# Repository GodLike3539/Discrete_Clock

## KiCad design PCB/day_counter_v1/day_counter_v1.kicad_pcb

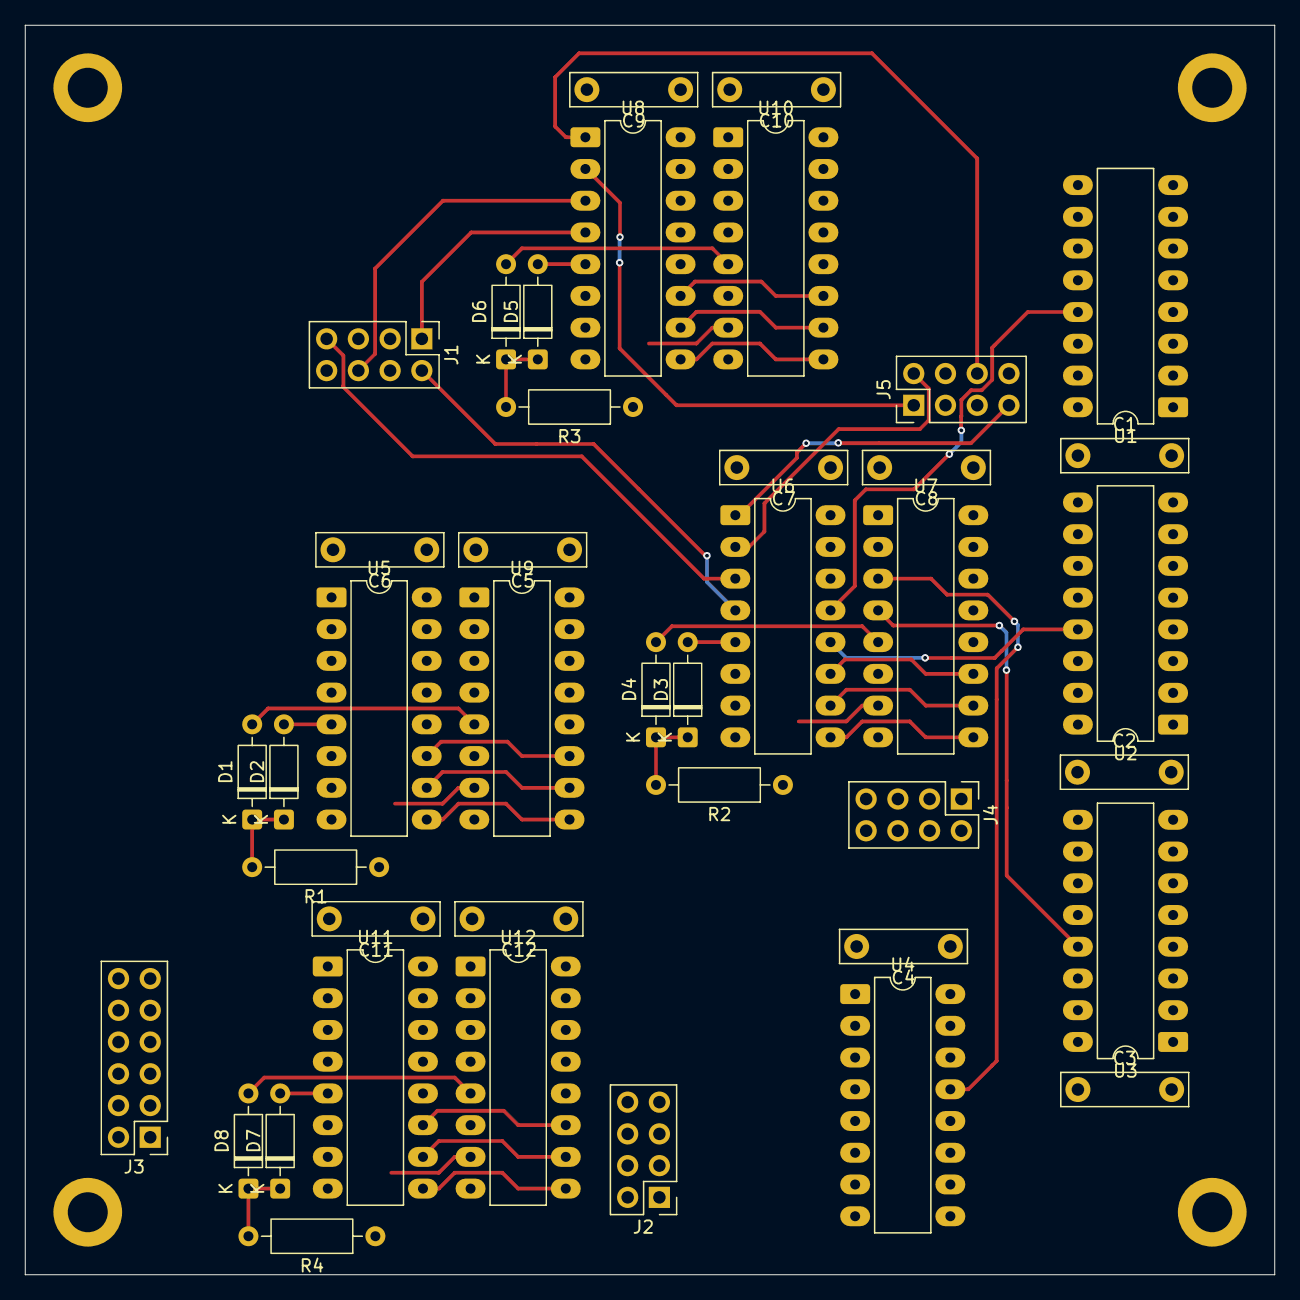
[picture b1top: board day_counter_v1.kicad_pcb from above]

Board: 2 copper layers, 100.0 x 100.0 mm, 45 parts (0 on the bottom side), 61 nets.

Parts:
C1, C2, C3, C4, C5, C6, C7, C8, C9, C10, C11, C12: C; C_Rect_L10.0mm_W2.5mm_P7.50mm_MKS4
D1, D2, D3, D4, D5, D6, D7, D8: 1N4148; D_DO-35_SOD27_P7.62mm_Horizontal
H1, H2, H3, H4: MountingHole_Pad; MountingHole_3.2mm_M3_ISO14580_Pad
J1, J2, J4, J5: Conn_02x04_Odd_Even; PinHeader_2x04_P2.54mm_Vertical
J3: Conn_02x06_Odd_Even; PinHeader_2x06_P2.54mm_Vertical
R1, R2, R3, R4: 1k; R_Axial_DIN0207_L6.3mm_D2.5mm_P10.16mm_Horizontal
U1, U2, U3, U4: 74LS160; DIP-16_W7.62mm_LongPads
U5, U6, U7, U8, U9, U10, U11, U12: 74LS151; DIP-16_W7.62mm_LongPads

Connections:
1PPD: J4.6, U1.7 (CEP)
1dA: U1.14 (Q0), U9.13 (I6)
1dB: U1.13 (Q1), U6.13 (I6)
1dC: U1.12 (Q2), U8.13 (I6)
1dD: U1.11 (Q3), U11.13 (I6)
1hA: J4.4, U9.15 (I4)
1hB: J4.2, U6.15 (I4)
1hC: J4.1, U8.15 (I4)
1hD: J4.3, U11.15 (I4)
1mA: J5.4, U9.2 (I2)
1mB: J5.2, U6.2 (I2)
1mC: J5.1, U8.2 (I2)
1mD: J5.3, U11.2 (I2)
1sA: J1.4, U9.4 (I0)
1sB: J1.2, U6.4 (I0)
1sC: J1.1, U8.4 (I0)
1sD: J1.3, U11.4 (I0)
10dA: U2.14 (Q0), U9.12 (I7)
10dB: U2.13 (Q1), U6.12 (I7)
10dC: U2.12 (Q2), U8.12 (I7)
10dD: U2.11 (Q3), U11.12 (I7)
10hA: J4.5, U9.14 (I5)
10hB: J4.7, U6.14 (I5)
10mA: J5.5, U9.1 (I3)
10mB: J5.7, U6.1 (I3)
10mC: J5.6, U8.1 (I3)
10sA: J1.5, U9.3 (I1)
10sB: J1.7, U6.3 (I1)
10sC: J1.6, U8.3 (I1)
50Hz: U1.2 (CP), U2.2 (CP), U3.2 (CP), U4.2 (CP)
100dA: U3.14 (Q0), U5.4 (I0)
100dB: U3.13 (Q1), U7.4 (I0)
100dC: U3.12 (Q2), U10.4 (I0)
100dD: U3.11 (Q3), U12.4 (I0)
1000dA: U4.14 (Q0), U5.3 (I1)
1000dB: U4.13 (Q1), U7.3 (I1)
1000dC: U4.12 (Q2), U10.3 (I1)
1000dD: U4.11 (Q3), U12.3 (I1)
+5V: C1.1, C2.1, C3.1, C4.1, C5.1, C6.1, C7.1, C8.1, C9.1, C10.1, C11.1, C12.1, J2.7, J2.8, J3.11, U1.1 (~MR), U1.9 (~PE), U1.10 (CET), U1.16 (VCC), U2.1 (~MR), U2.9 (~PE), U2.10 (CET), U2.16 (VCC), U3.1 (~MR), U3.9 (~PE), U3.10 (CET), U3.16 (VCC), U4.1 (~MR), U4.9 (~PE), U4.10 (CET), U4.16 (VCC), U5.16 (VCC), U6.16 (VCC), U7.16 (VCC), U8.16 (VCC), U9.16 (VCC), U10.16 (VCC), U11.16 (VCC), U12.16 (VCC)
A: D1.1 (K), D2.1 (K), J3.1, R1.2
B: D3.1 (K), D4.1 (K), J3.2, R2.2
C: D5.1 (K), D6.1 (K), J3.3, R3.2
CLK50: J2.5, J3.10
D: D7.1 (K), D8.1 (K), J3.4, R4.2
GND: C1.2, C2.2, C3.2, C4.2, C5.2, C6.2, C7.2, C8.2, C9.2, C10.2, C11.2, C12.2, J1.8, J2.1, J2.2, J3.12, J4.8, J5.8, R1.1, R2.1, R3.1, R4.1, U1.3 (D0), U1.4 (D1), U1.5 (D2), U1.6 (D3), U1.8 (GND), U2.3 (D0), U2.4 (D1), U2.5 (D2), U2.6 (D3), U2.8 (GND), U3.3 (D0), U3.4 (D1), U3.5 (D2), U3.6 (D3), U3.8 (GND), U4.3 (D0), U4.4 (D1), U4.5 (D2), U4.6 (D3), U4.8 (GND), U5.8 (GND), U6.8 (GND), U7.8 (GND), U8.8 (GND), U9.8 (GND), U10.8 (GND), U11.8 (GND), U12.8 (GND)
unnamed: D1.2 (A), U9.5 (Z)
unnamed: D2.2 (A), U5.5 (Z)
unnamed: D3.2 (A), U6.5 (Z)
unnamed: D4.2 (A), U7.5 (Z)
unnamed: D5.2 (A), U8.5 (Z)
unnamed: D6.2 (A), U10.5 (Z)
unnamed: D7.2 (A), U11.5 (Z)
unnamed: D8.2 (A), U12.5 (Z)
unnamed: U1.15 (TC), U2.7 (CEP)
unnamed: U2.15 (TC), U3.7 (CEP)
unnamed: U3.15 (TC), U4.7 (CEP)
Sel_A: J3.5, U5.11 (S0), U6.11 (S0), U7.11 (S0), U8.11 (S0), U9.11 (S0), U10.11 (S0), U11.11 (S0), U12.11 (S0)
Sel_B: J3.6, U5.10 (S1), U6.10 (S1), U7.10 (S1), U8.10 (S1), U9.10 (S1), U10.10 (S1), U11.10 (S1), U12.10 (S1)
Sel_C: J3.7, U5.9 (S2), U6.9 (S2), U7.9 (S2), U8.9 (S2), U9.9 (S2), U10.9 (S2), U11.9 (S2), U12.9 (S2)
Sel_D: J3.8, U6.7 (~E), U8.7 (~E), U9.7 (~E), U11.7 (~E)
~Sel_D: J3.9, U5.7 (~E), U7.7 (~E), U10.7 (~E), U12.7 (~E)

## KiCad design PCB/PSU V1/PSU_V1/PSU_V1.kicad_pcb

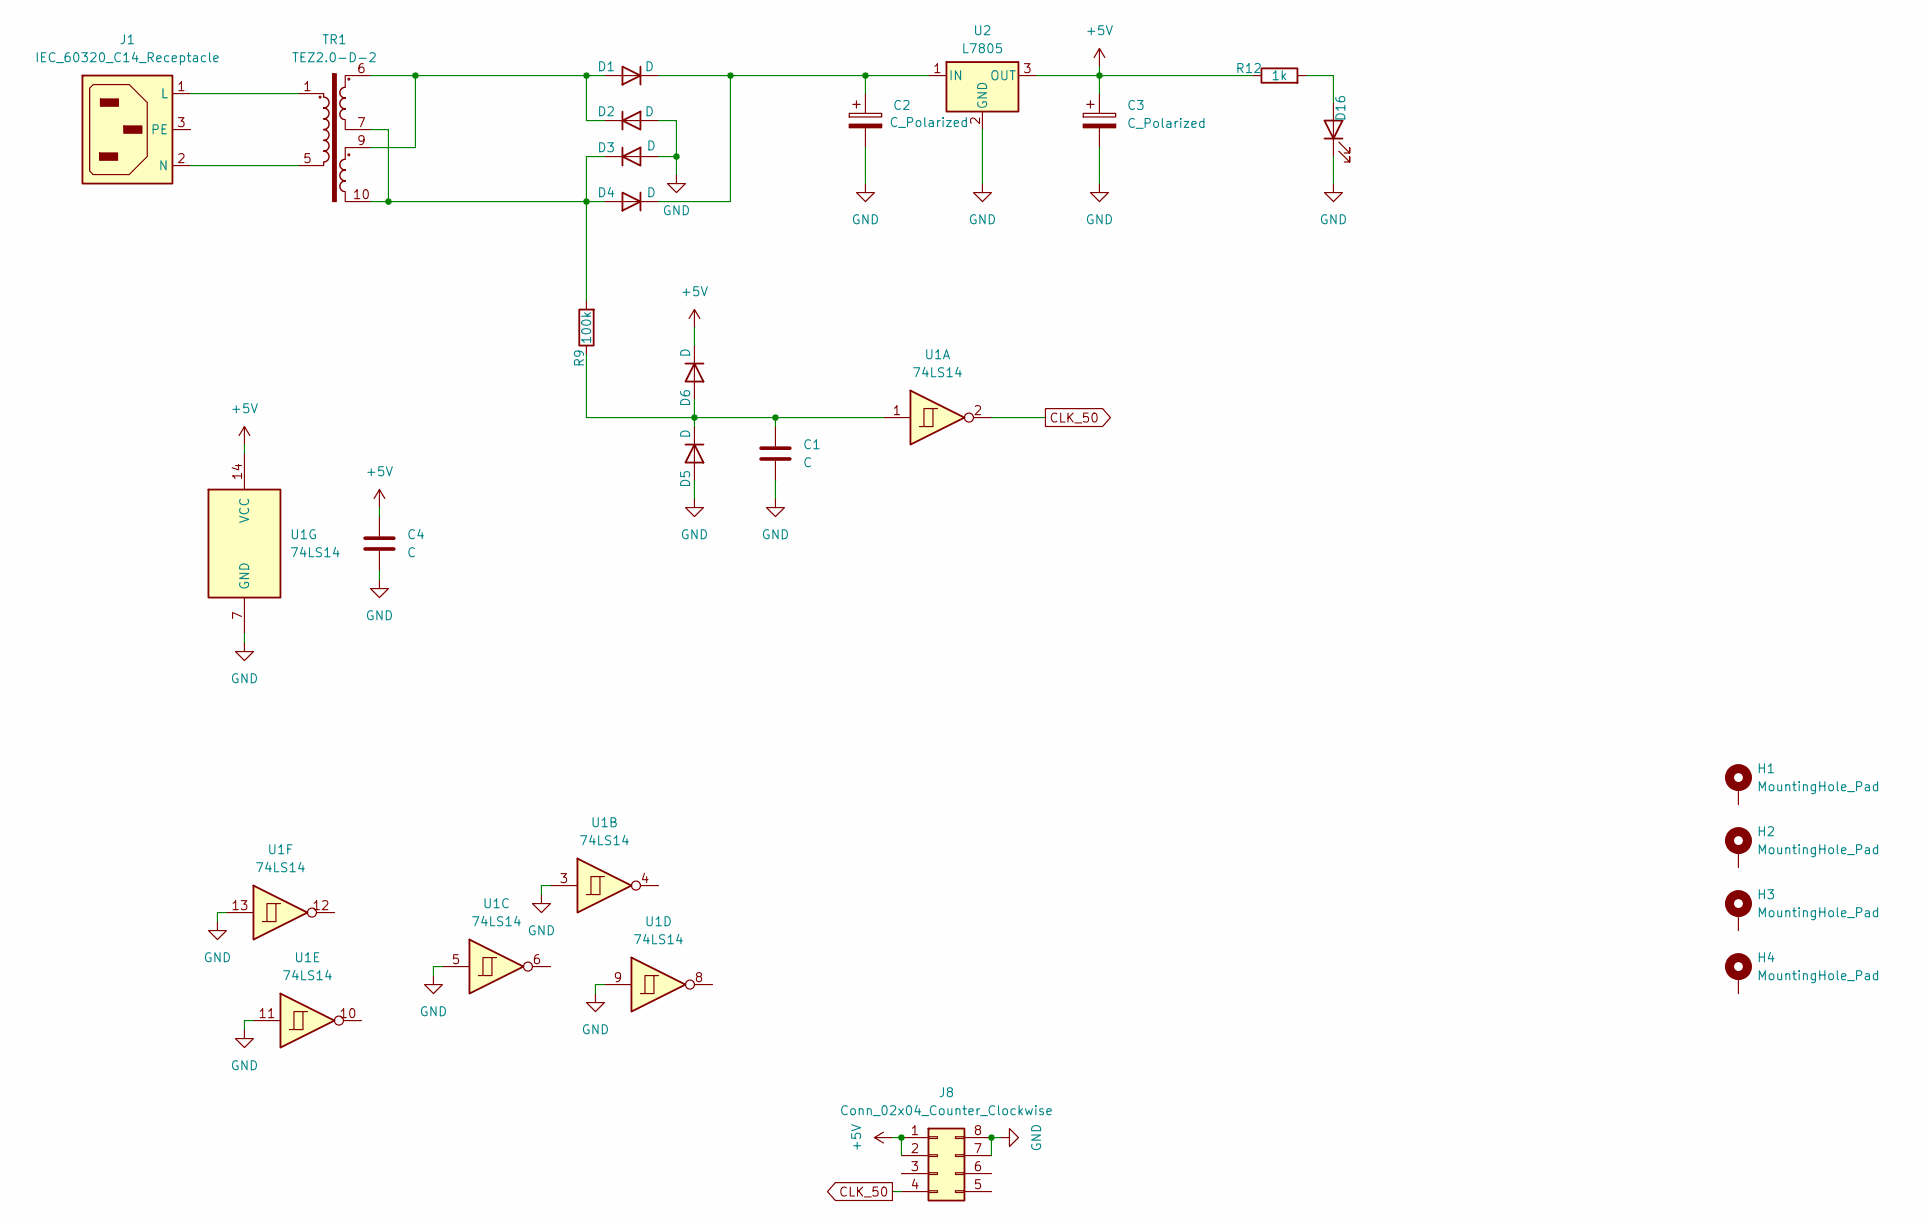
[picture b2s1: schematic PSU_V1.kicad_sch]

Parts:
C1, C4: C; C_Rect_L10.0mm_W2.5mm_P7.50mm_MKS4
C2, C3: C_Polarized; CP_Radial_D12.5mm_P7.50mm
D1, D2, D3, D4, D5, D6: D; D_DO-35_SOD27_P10.16mm_Horizontal
D16: LED; LED_D3.0mm
H1, H2, H3, H4: MountingHole_Pad; MountingHole_3.2mm_M3_DIN965_Pad
J1: IEC_60320_C14_Receptacle; GSF1220161
J8: Conn_02x04_Counter_Clockwise; IDC-Header_2x04_P2.54mm_Vertical
R9: 100k; R_Axial_DIN0207_L6.3mm_D2.5mm_P10.16mm_Horizontal
R12: 1k; R_Axial_DIN0207_L6.3mm_D2.5mm_P10.16mm_Horizontal
TR1: TEZ2.0-D-2; Transformer_CHK_EI42-5VA_2xSec
U1: 74LS14; DIP-14_W7.62mm_LongPads
U2: L7805; TO-220-3_Horizontal_TabDown

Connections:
+5V: C3.1, C4.1, D6.1 (K), J8.1, J8.2, R12.1, U1.14 (VCC), U2.3 (OUT)
CLK_50: J8.4, U1.2
GND: C1.2, C2.2, C3.2, C4.2, D2.2 (A), D3.2 (A), D5.2 (A), D16.1 (K), J8.7, J8.8, U1.3, U1.5, U1.7 (GND), U1.9, U1.11, U1.13, U2.2 (GND)
unnamed: D1.2 (A), D2.1 (K), TR1.6, TR1.9
unnamed: C2.1, D1.1 (K), D4.1 (K), U2.1 (IN)
unnamed: D3.1 (K), D4.2 (A), R9.2, TR1.7, TR1.10
unnamed: C1.1, D5.1 (K), D6.2 (A), R9.1, U1.1
unnamed: D16.2 (A), R12.2
unnamed: J1.1 (L), TR1.1
unnamed: J1.2 (N), TR1.5

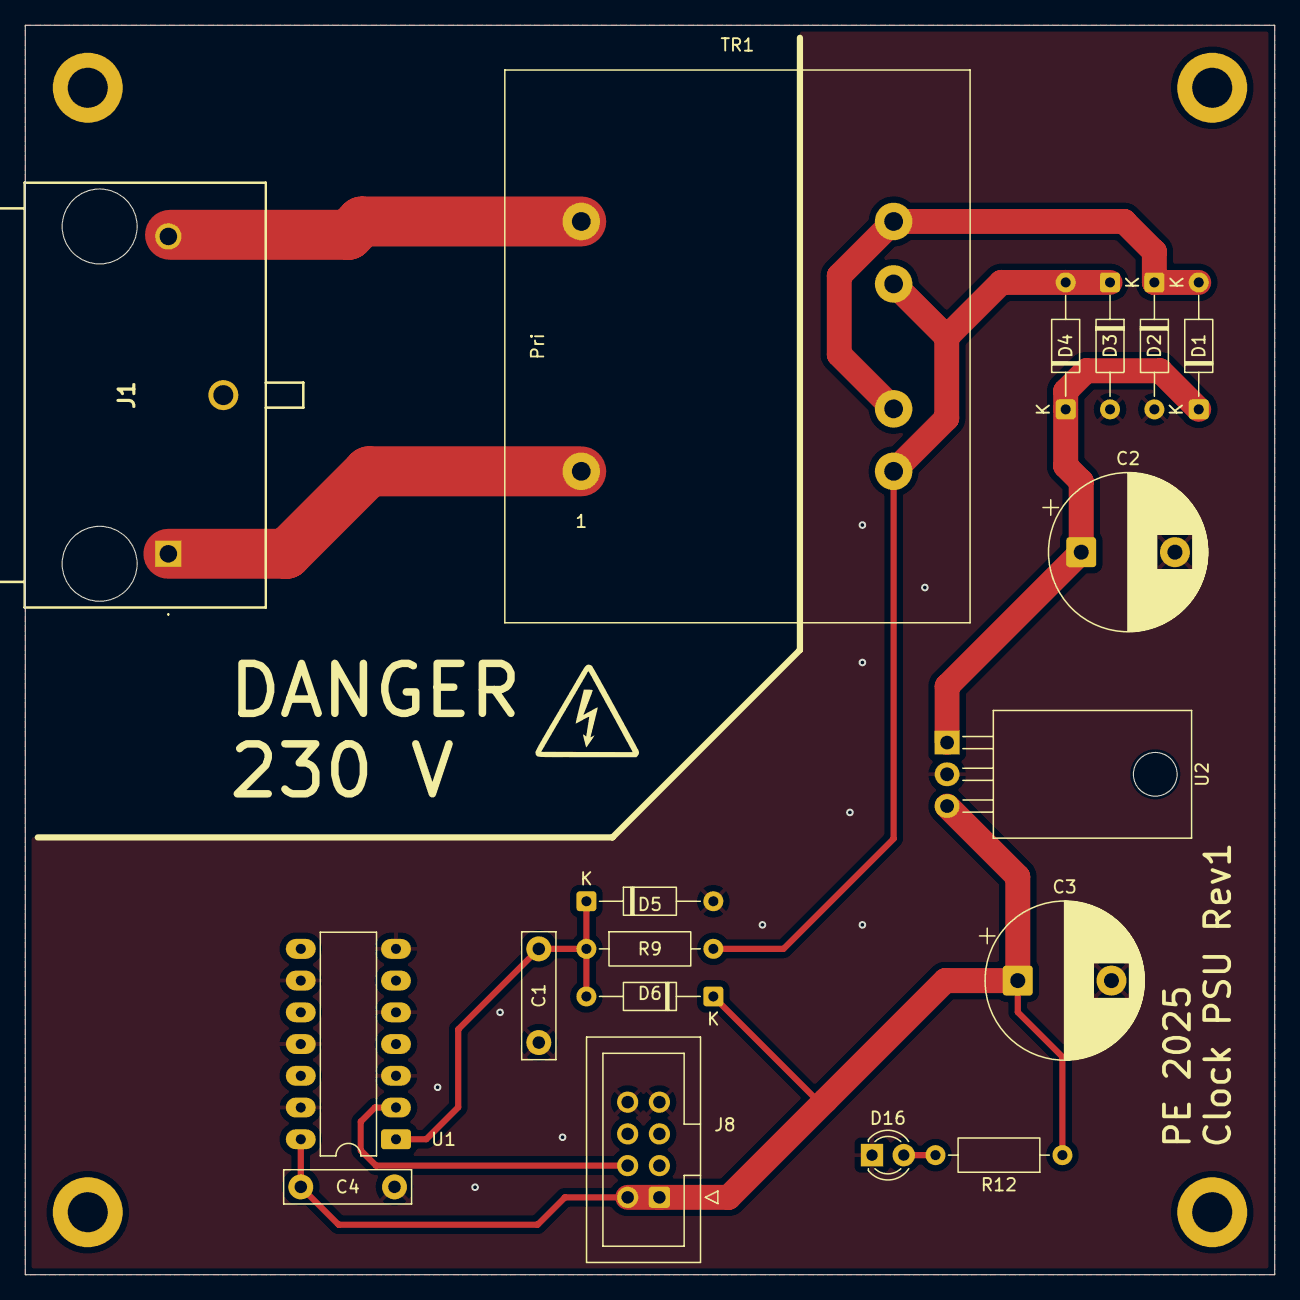
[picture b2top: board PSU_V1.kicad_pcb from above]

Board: 2 copper layers, 100.0 x 100.0 mm, 22 parts (0 on the bottom side), 10 nets.

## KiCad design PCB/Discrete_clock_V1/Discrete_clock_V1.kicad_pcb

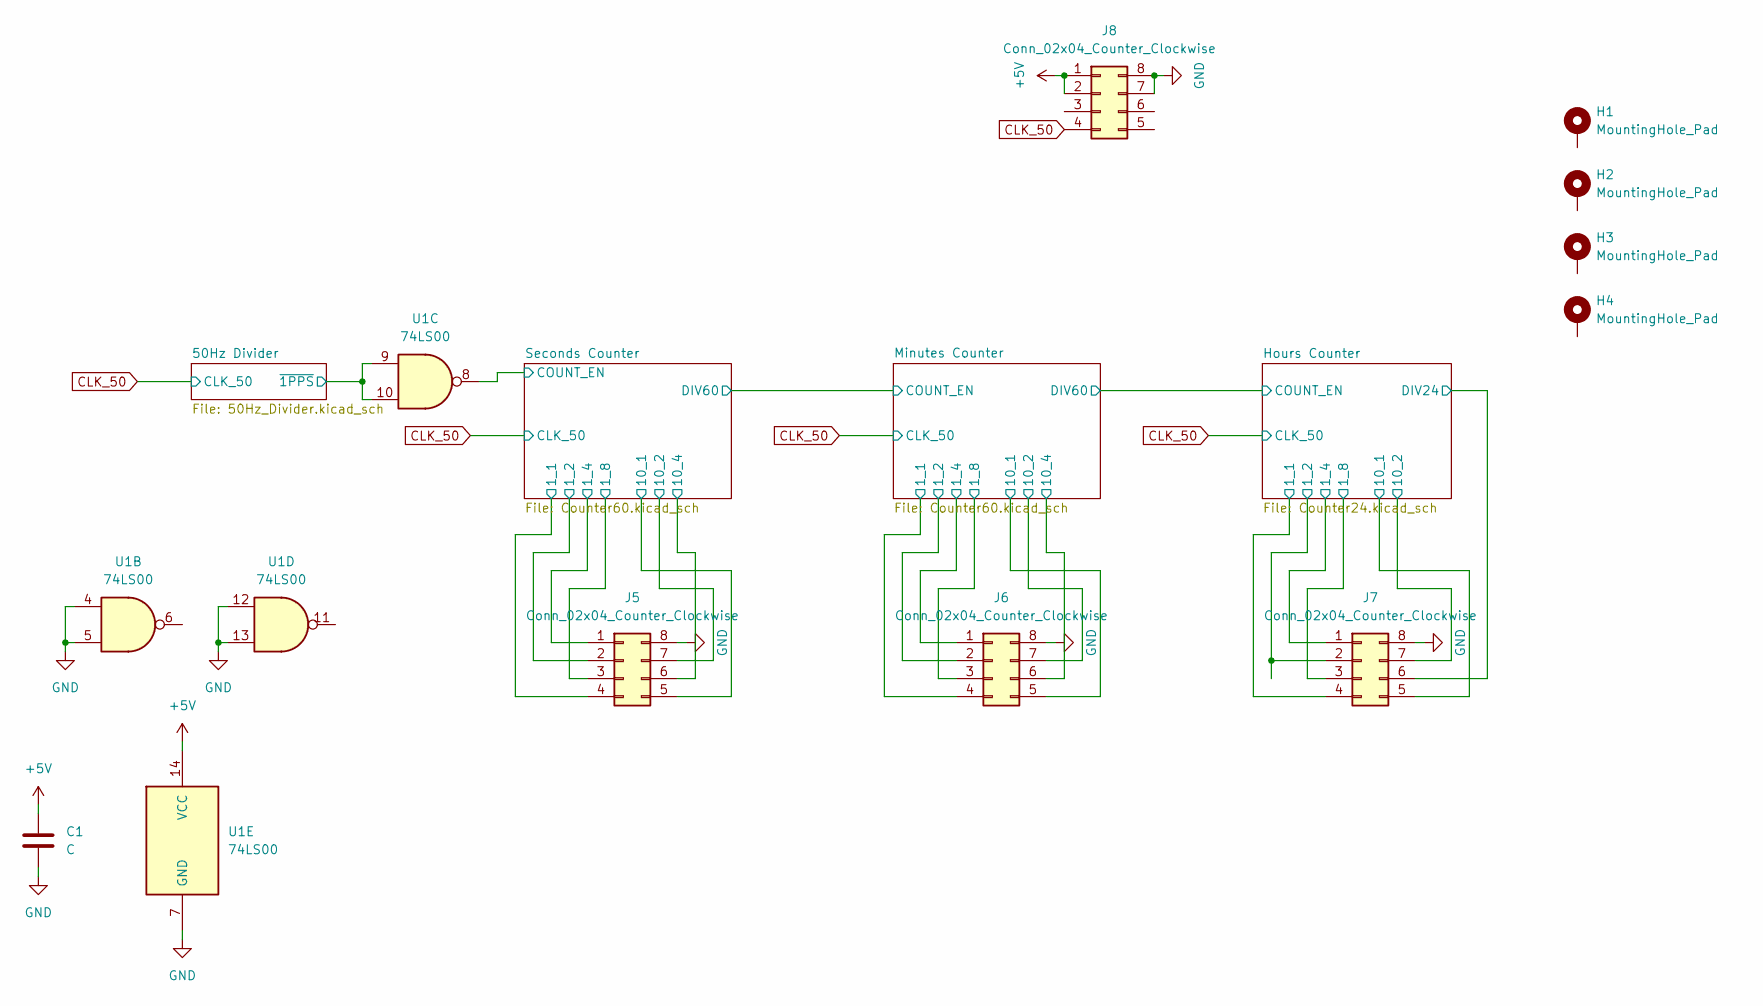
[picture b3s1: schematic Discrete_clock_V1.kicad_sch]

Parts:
C1: C; C_Rect_L10.0mm_W2.5mm_P7.50mm_MKS4
H1, H2, H3, H4: MountingHole_Pad; MountingHole_3.2mm_M3_DIN965_Pad
J5, J6, J7, J8: Conn_02x04_Counter_Clockwise; IDC-Header_2x04_P2.54mm_Vertical
U1: 74LS00; DIP-14_W7.62mm_LongPads

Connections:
+5V: C1.1, J8.1, J8.2, U1.14 (VCC); also elsewhere on the board
/50Hz Divider/~1PPS: U1.9, U1.10; also elsewhere on the board
/Hours Counter/1_1: J7.4; also elsewhere on the board
/Hours Counter/1_2: J7.2; also elsewhere on the board
/Hours Counter/1_4: J7.1; also elsewhere on the board
/Hours Counter/1_8: J7.3; also elsewhere on the board
/Hours Counter/10_1: J7.5; also elsewhere on the board
/Hours Counter/10_2: J7.7; also elsewhere on the board
/Hours Counter/DIV24: J7.6; also elsewhere on the board
/Minutes Counter/1_1: J6.4; also elsewhere on the board
/Minutes Counter/1_2: J6.2; also elsewhere on the board
/Minutes Counter/1_4: J6.1; also elsewhere on the board
/Minutes Counter/1_8: J6.3; also elsewhere on the board
/Minutes Counter/10_1: J6.5; also elsewhere on the board
/Minutes Counter/10_2: J6.7; also elsewhere on the board
/Minutes Counter/10_4: J6.6; also elsewhere on the board
/Seconds Counter/1_1: J5.4; also elsewhere on the board
/Seconds Counter/1_2: J5.2; also elsewhere on the board
/Seconds Counter/1_4: J5.1; also elsewhere on the board
/Seconds Counter/1_8: J5.3; also elsewhere on the board
/Seconds Counter/10_1: J5.5; also elsewhere on the board
/Seconds Counter/10_2: J5.7; also elsewhere on the board
/Seconds Counter/10_4: J5.6; also elsewhere on the board
/Seconds Counter/COUNT_EN: U1.8; also elsewhere on the board
CLK_50: J8.4; also elsewhere on the board
GND: C1.2, J5.8, J6.8, J7.8, J8.7, J8.8, U1.4, U1.5, U1.7 (GND), U1.12, U1.13; also elsewhere on the board

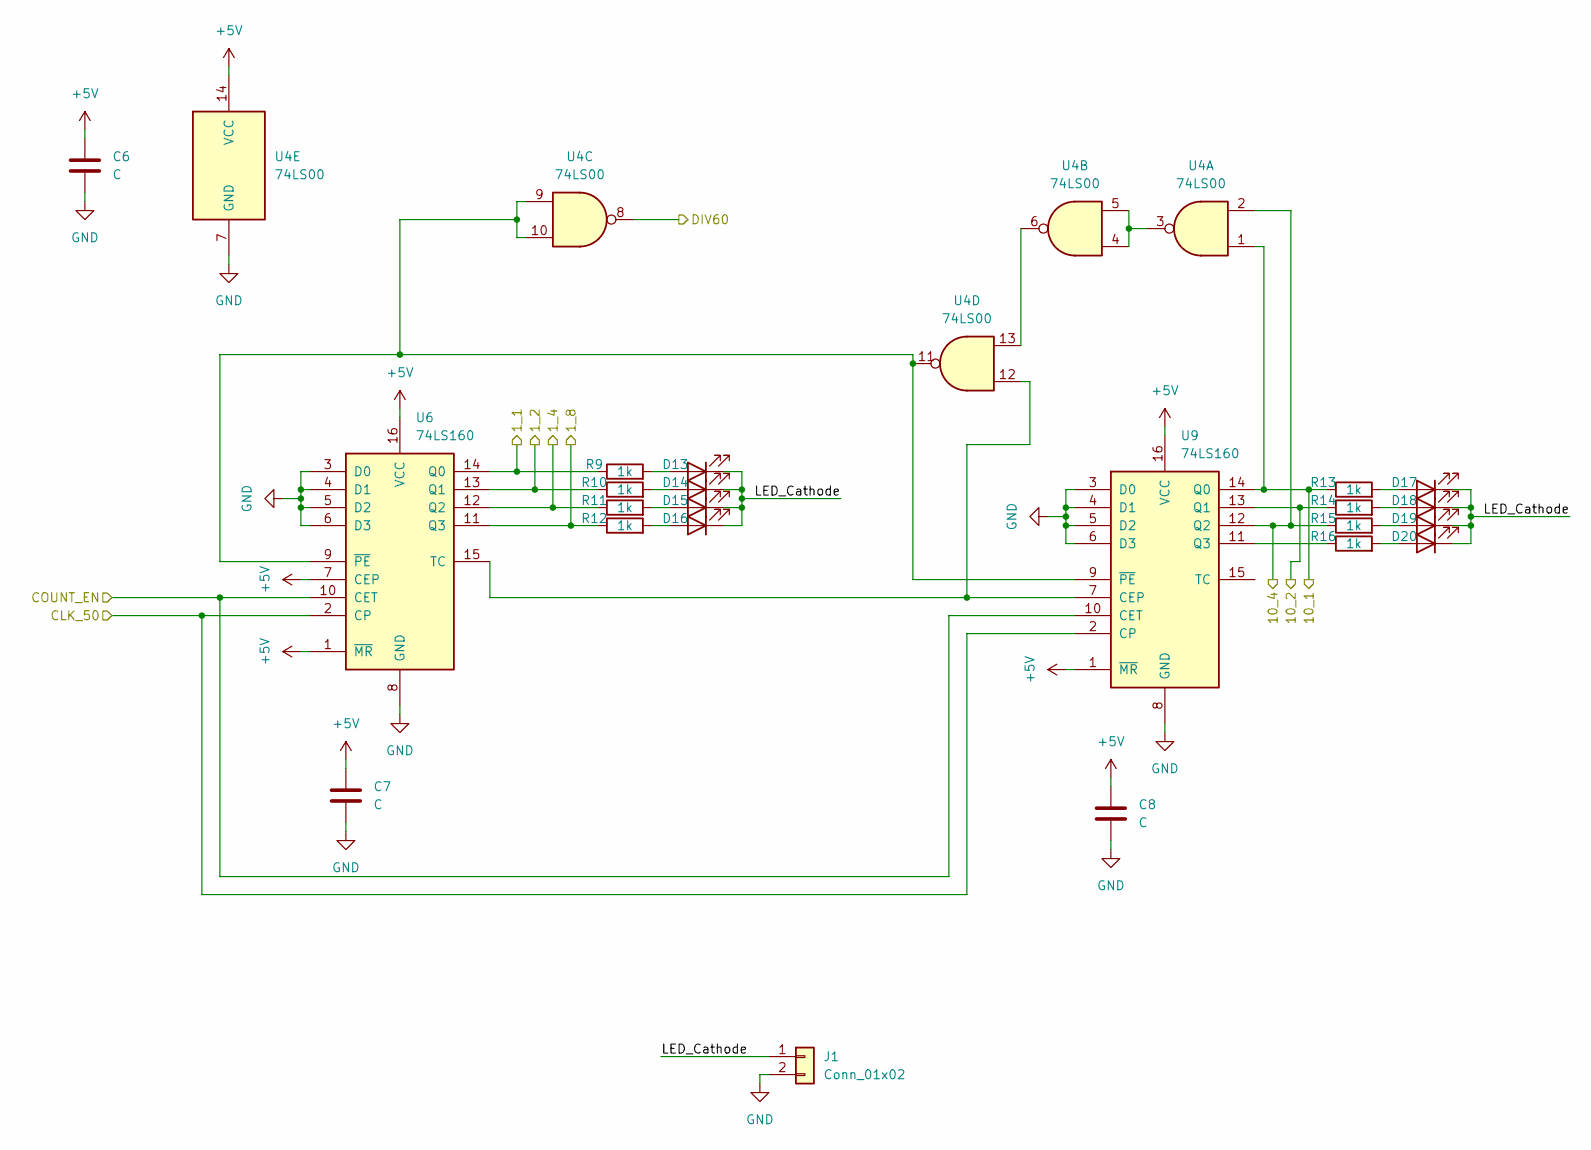
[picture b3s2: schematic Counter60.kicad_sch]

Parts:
C6, C7, C8: C; C_Rect_L10.0mm_W2.5mm_P7.50mm_MKS4
D13, D14, D15, D16, D17, D18, D19, D20: LED; LED_D3.0mm
J1: Conn_01x02; PinHeader_1x02_P2.54mm_Vertical
R9, R10, R11, R12, R13, R14, R15, R16: 1k; R_Axial_DIN0207_L6.3mm_D2.5mm_P10.16mm_Horizontal
U4: 74LS00; DIP-14_W7.62mm_LongPads
U6, U9: 74LS160; DIP-16_W7.62mm_LongPads

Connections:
+5V: C6.1, C7.1, C8.1, U4.14 (VCC), U6.1 (~MR), U6.7 (CEP), U6.16 (VCC), U9.1 (~MR), U9.16 (VCC); also elsewhere on the board
/Minutes Counter/COUNT_EN: U4.8; also elsewhere on the board
/Seconds Counter/1_1: R9.1, U6.14 (Q0); also elsewhere on the board
/Seconds Counter/1_2: R10.1, U6.13 (Q1); also elsewhere on the board
/Seconds Counter/1_4: R11.1, U6.12 (Q2); also elsewhere on the board
/Seconds Counter/1_8: R12.1, U6.11 (Q3); also elsewhere on the board
/Seconds Counter/10_1: R13.1, U4.1, U9.14 (Q0); also elsewhere on the board
/Seconds Counter/10_2: R14.1, U9.13 (Q1); also elsewhere on the board
/Seconds Counter/10_4: R15.1, U4.2, U9.12 (Q2); also elsewhere on the board
/Seconds Counter/COUNT_EN: U6.10 (CET), U9.10 (CET); also elsewhere on the board
/Seconds Counter/LED_Cathode: D13.1 (K), D14.1 (K), D15.1 (K), D16.1 (K), D17.1 (K), D18.1 (K), D19.1 (K), D20.1 (K), J1.1
CLK_50: U6.2 (CP), U9.2 (CP); also elsewhere on the board
GND: C6.2, C7.2, C8.2, J1.2, U4.7 (GND), U6.3 (D0), U6.4 (D1), U6.5 (D2), U6.6 (D3), U6.8 (GND), U9.3 (D0), U9.4 (D1), U9.5 (D2), U9.6 (D3), U9.8 (GND); also elsewhere on the board
unnamed: D13.2 (A), R9.2
unnamed: D14.2 (A), R10.2
unnamed: D15.2 (A), R11.2
unnamed: D16.2 (A), R12.2
unnamed: D17.2 (A), R13.2
unnamed: D18.2 (A), R14.2
unnamed: D19.2 (A), R15.2
unnamed: D20.2 (A), R16.2
unnamed: U4.3, U4.4, U4.5
unnamed: U4.6, U4.13
unnamed: U4.12, U6.15 (TC), U9.7 (CEP)
unnamed: U4.9, U4.10, U4.11, U6.9 (~PE), U9.9 (~PE)
unnamed: R16.1, U9.11 (Q3)

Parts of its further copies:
C9, C10, C11: C; C_Rect_L10.0mm_W2.5mm_P7.50mm_MKS4
D21, D22, D23, D24, D25, D26, D27, D28: LED; LED_D3.0mm
J2: Conn_01x02; PinHeader_1x02_P2.54mm_Vertical
R17, R18, R19, R20, R21, R22, R23, R24: 1k; R_Axial_DIN0207_L6.3mm_D2.5mm_P10.16mm_Horizontal
U7: 74LS00; DIP-14_W7.62mm_LongPads
U10, U12: 74LS160; DIP-16_W7.62mm_LongPads

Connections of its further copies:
+5V: C9.1, C10.1, C11.1, U7.14 (VCC), U10.1 (~MR), U10.7 (CEP), U10.16 (VCC), U12.1 (~MR), U12.16 (VCC); also elsewhere on the board
/Hours Counter/COUNT_EN: U7.11; also elsewhere on the board
/Minutes Counter/1_1: R17.1, U10.14 (Q0); also elsewhere on the board
/Minutes Counter/1_2: R18.1, U10.13 (Q1); also elsewhere on the board
/Minutes Counter/1_4: R19.1, U10.12 (Q2); also elsewhere on the board
/Minutes Counter/1_8: R20.1, U10.11 (Q3); also elsewhere on the board
/Minutes Counter/10_1: R21.1, U7.1, U12.14 (Q0); also elsewhere on the board
/Minutes Counter/10_2: R22.1, U12.13 (Q1); also elsewhere on the board
/Minutes Counter/10_4: R23.1, U7.2, U12.12 (Q2); also elsewhere on the board
/Minutes Counter/COUNT_EN: U10.10 (CET), U12.10 (CET); also elsewhere on the board
/Minutes Counter/LED_Cathode: D21.1 (K), D22.1 (K), D23.1 (K), D24.1 (K), D25.1 (K), D26.1 (K), D27.1 (K), D28.1 (K), J2.1
CLK_50: U10.2 (CP), U12.2 (CP); also elsewhere on the board
GND: C9.2, C10.2, C11.2, J2.2, U7.7 (GND), U10.3 (D0), U10.4 (D1), U10.5 (D2), U10.6 (D3), U10.8 (GND), U12.3 (D0), U12.4 (D1), U12.5 (D2), U12.6 (D3), U12.8 (GND); also elsewhere on the board
unnamed: D21.2 (A), R17.2
unnamed: D22.2 (A), R18.2
unnamed: D23.2 (A), R19.2
unnamed: D24.2 (A), R20.2
unnamed: D25.2 (A), R21.2
unnamed: D26.2 (A), R22.2
unnamed: D27.2 (A), R23.2
unnamed: D28.2 (A), R24.2
unnamed: U7.3, U7.4, U7.5
unnamed: U7.6, U7.10
unnamed: U7.9, U10.15 (TC), U12.7 (CEP)
unnamed: U7.8, U7.12, U7.13, U10.9 (~PE), U12.9 (~PE)
unnamed: R24.1, U12.11 (Q3)

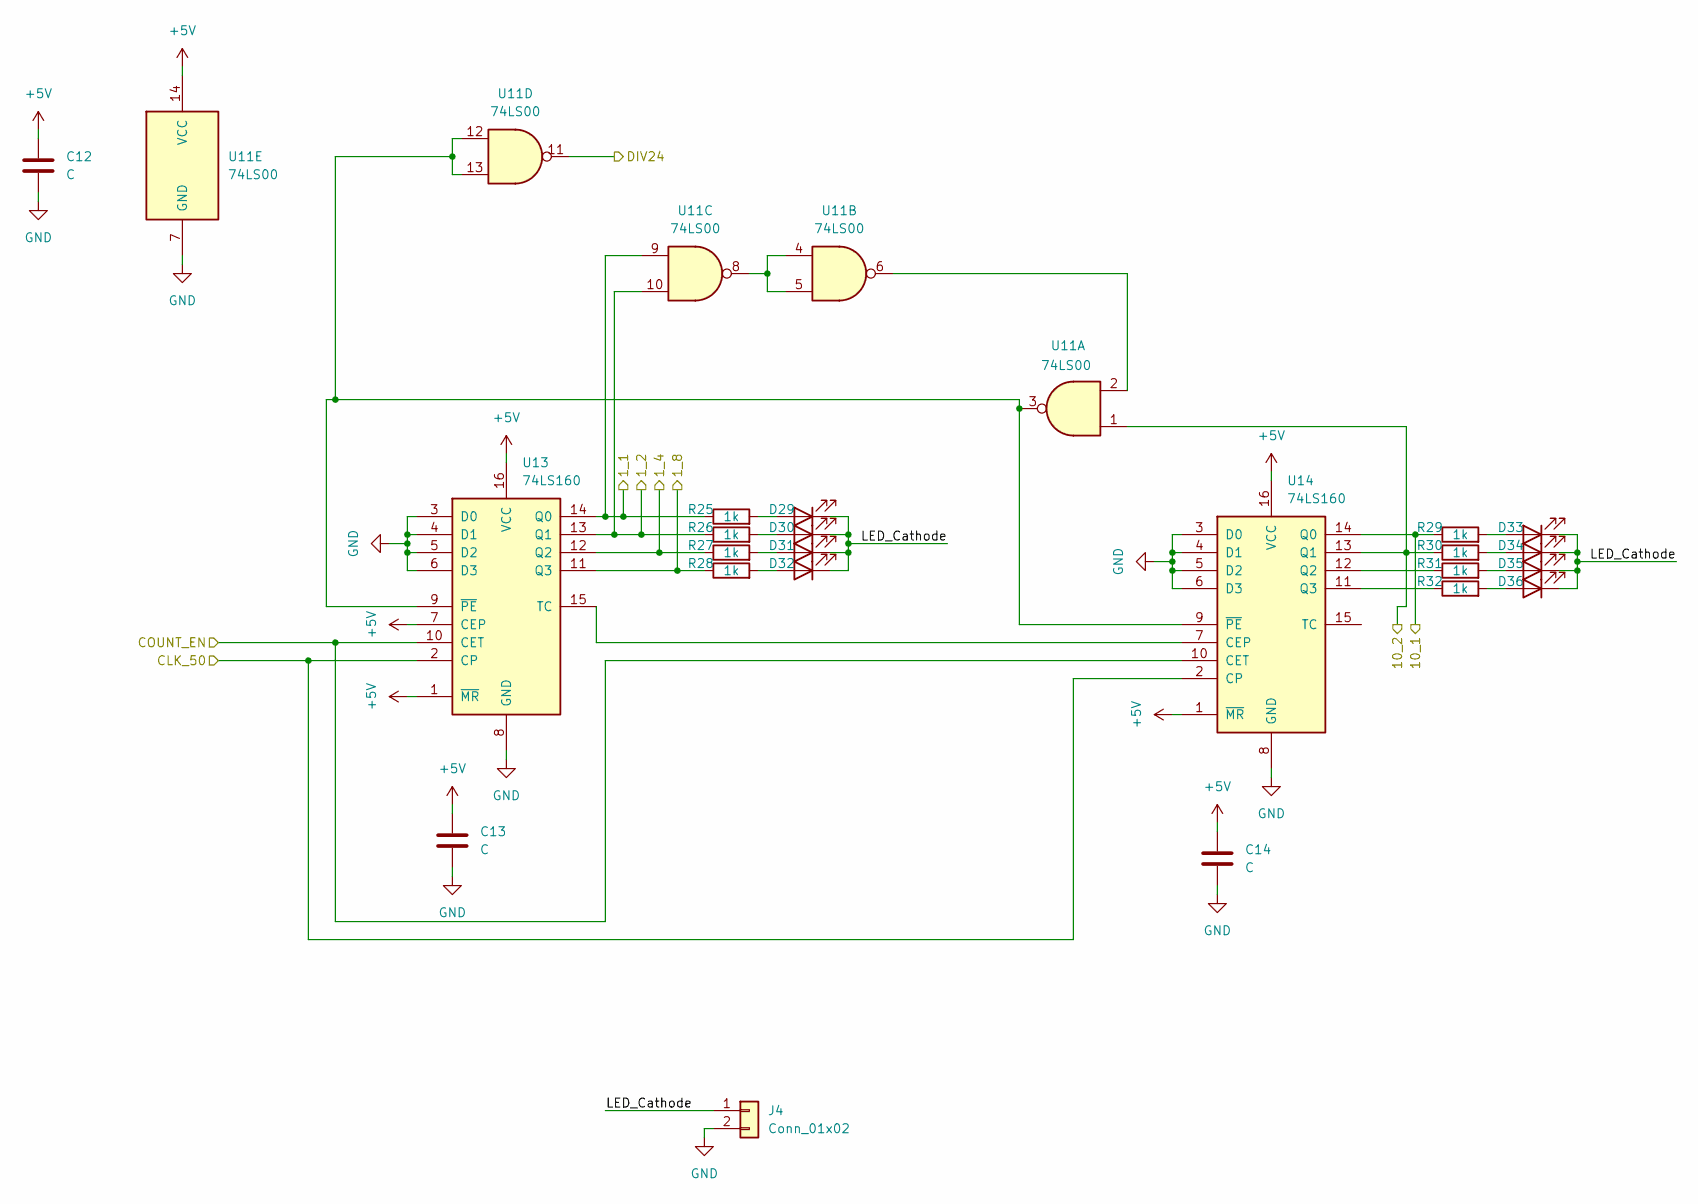
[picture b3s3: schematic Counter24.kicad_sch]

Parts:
C12, C13, C14: C; C_Rect_L10.0mm_W2.5mm_P7.50mm_MKS4
D29, D30, D31, D32, D33, D34, D35, D36: LED; LED_D3.0mm
J4: Conn_01x02; PinHeader_1x02_P2.54mm_Vertical
R25, R26, R27, R28, R29, R30, R31, R32: 1k; R_Axial_DIN0207_L6.3mm_D2.5mm_P10.16mm_Horizontal
U11: 74LS00; DIP-14_W7.62mm_LongPads
U13, U14: 74LS160; DIP-16_W7.62mm_LongPads

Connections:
+5V: C12.1, C13.1, C14.1, U11.14 (VCC), U13.1 (~MR), U13.7 (CEP), U13.16 (VCC), U14.1 (~MR), U14.16 (VCC); also elsewhere on the board
/Hours Counter/1_1: R25.1, U11.9, U13.14 (Q0); also elsewhere on the board
/Hours Counter/1_2: R26.1, U11.10, U13.13 (Q1); also elsewhere on the board
/Hours Counter/1_4: R27.1, U13.12 (Q2); also elsewhere on the board
/Hours Counter/1_8: R28.1, U13.11 (Q3); also elsewhere on the board
/Hours Counter/10_1: R29.1, U14.14 (Q0); also elsewhere on the board
/Hours Counter/10_2: R30.1, U11.1, U14.13 (Q1); also elsewhere on the board
/Hours Counter/COUNT_EN: U13.10 (CET), U14.10 (CET); also elsewhere on the board
/Hours Counter/DIV24: U11.11; also elsewhere on the board
/Hours Counter/LED_Cathode: D29.1 (K), D30.1 (K), D31.1 (K), D32.1 (K), D33.1 (K), D34.1 (K), D35.1 (K), D36.1 (K), J4.1
CLK_50: U13.2 (CP), U14.2 (CP); also elsewhere on the board
GND: C12.2, C13.2, C14.2, J4.2, U11.7 (GND), U13.3 (D0), U13.4 (D1), U13.5 (D2), U13.6 (D3), U13.8 (GND), U14.3 (D0), U14.4 (D1), U14.5 (D2), U14.6 (D3), U14.8 (GND); also elsewhere on the board
unnamed: D29.2 (A), R25.2
unnamed: D30.2 (A), R26.2
unnamed: D31.2 (A), R27.2
unnamed: D32.2 (A), R28.2
unnamed: D33.2 (A), R29.2
unnamed: D34.2 (A), R30.2
unnamed: D35.2 (A), R31.2
unnamed: D36.2 (A), R32.2
unnamed: U11.2, U11.6
unnamed: U11.4, U11.5, U11.8
unnamed: U13.15 (TC), U14.7 (CEP)
unnamed: U11.3, U11.12, U11.13, U13.9 (~PE), U14.9 (~PE)
unnamed: R31.1, U14.12 (Q2)
unnamed: R32.1, U14.11 (Q3)

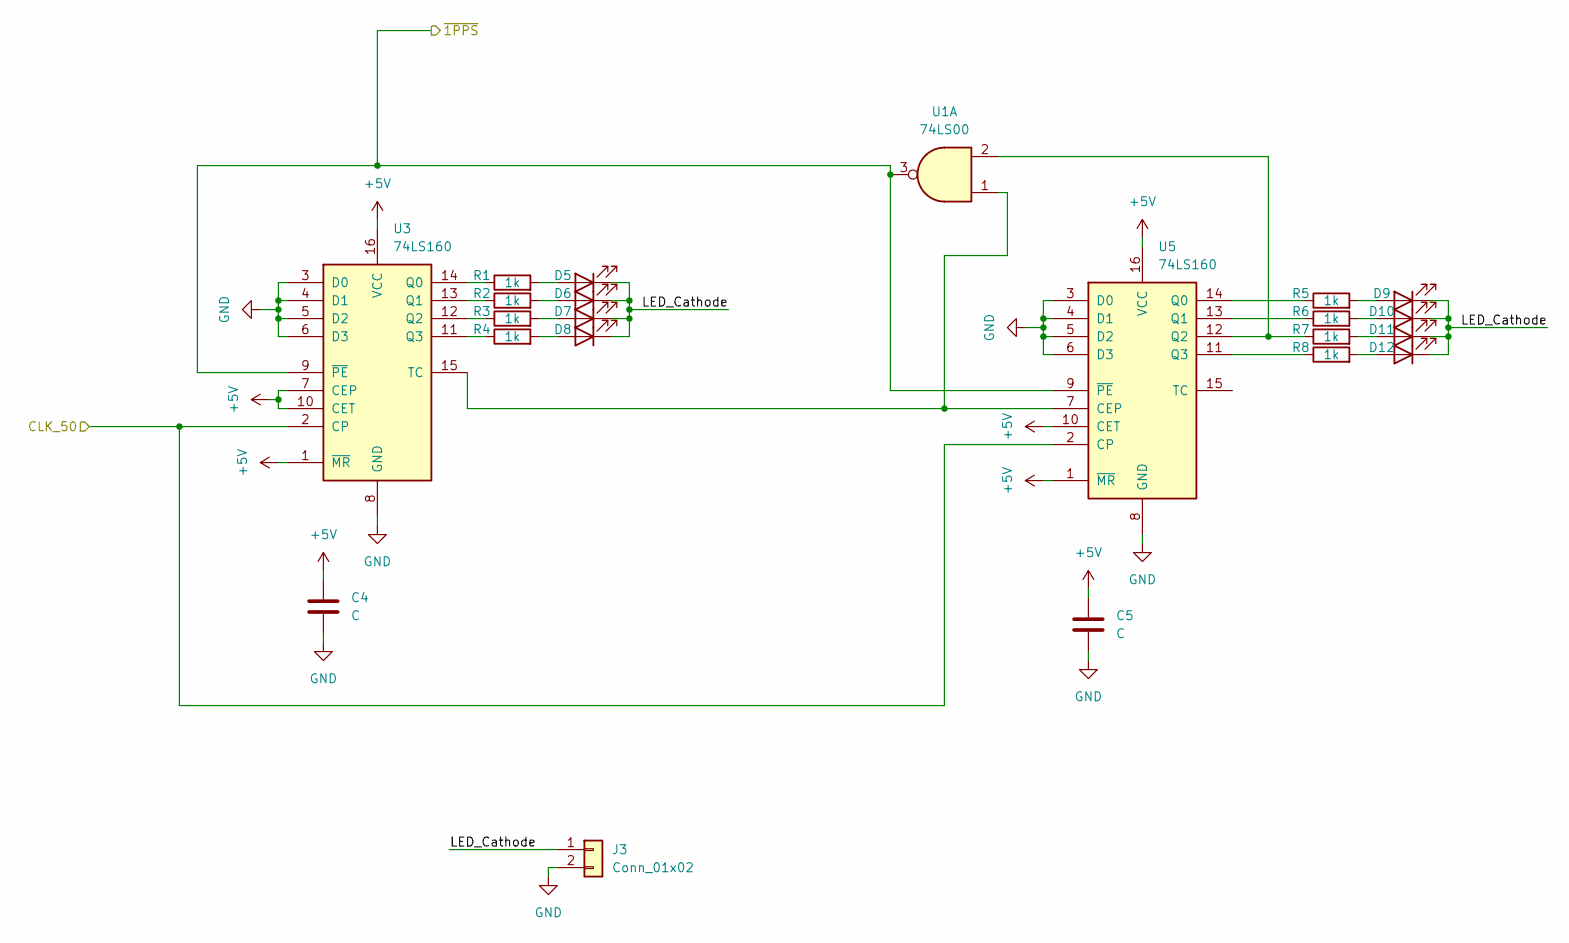
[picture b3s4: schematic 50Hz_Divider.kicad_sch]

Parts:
C4, C5: C; C_Rect_L10.0mm_W2.5mm_P7.50mm_MKS4
D5, D6, D7, D8, D9, D10, D11, D12: LED; LED_D3.0mm
J3: Conn_01x02; PinHeader_1x02_P2.54mm_Vertical
R1, R2, R3, R4, R5, R6, R7, R8: 1k; R_Axial_DIN0207_L6.3mm_D2.5mm_P10.16mm_Horizontal
U1: 74LS00; DIP-14_W7.62mm_LongPads
U3, U5: 74LS160; DIP-16_W7.62mm_LongPads

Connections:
+5V: C4.1, C5.1, U3.1 (~MR), U3.7 (CEP), U3.10 (CET), U3.16 (VCC), U5.1 (~MR), U5.10 (CET), U5.16 (VCC); also elsewhere on the board
/50Hz Divider/LED_Cathode: D5.1 (K), D6.1 (K), D7.1 (K), D8.1 (K), D9.1 (K), D10.1 (K), D11.1 (K), D12.1 (K), J3.1
/50Hz Divider/~1PPS: U1.3, U3.9 (~PE), U5.9 (~PE); also elsewhere on the board
CLK_50: U3.2 (CP), U5.2 (CP); also elsewhere on the board
GND: C4.2, C5.2, J3.2, U3.3 (D0), U3.4 (D1), U3.5 (D2), U3.6 (D3), U3.8 (GND), U5.3 (D0), U5.4 (D1), U5.5 (D2), U5.6 (D3), U5.8 (GND); also elsewhere on the board
unnamed: D5.2 (A), R1.2
unnamed: D6.2 (A), R2.2
unnamed: D7.2 (A), R3.2
unnamed: D8.2 (A), R4.2
unnamed: D9.2 (A), R5.2
unnamed: D10.2 (A), R6.2
unnamed: D11.2 (A), R7.2
unnamed: D12.2 (A), R8.2
unnamed: R1.1, U3.14 (Q0)
unnamed: R2.1, U3.13 (Q1)
unnamed: R3.1, U3.12 (Q2)
unnamed: R4.1, U3.11 (Q3)
unnamed: U1.1, U3.15 (TC), U5.7 (CEP)
unnamed: R5.1, U5.14 (Q0)
unnamed: R6.1, U5.13 (Q1)
unnamed: R7.1, U1.2, U5.12 (Q2)
unnamed: R8.1, U5.11 (Q3)

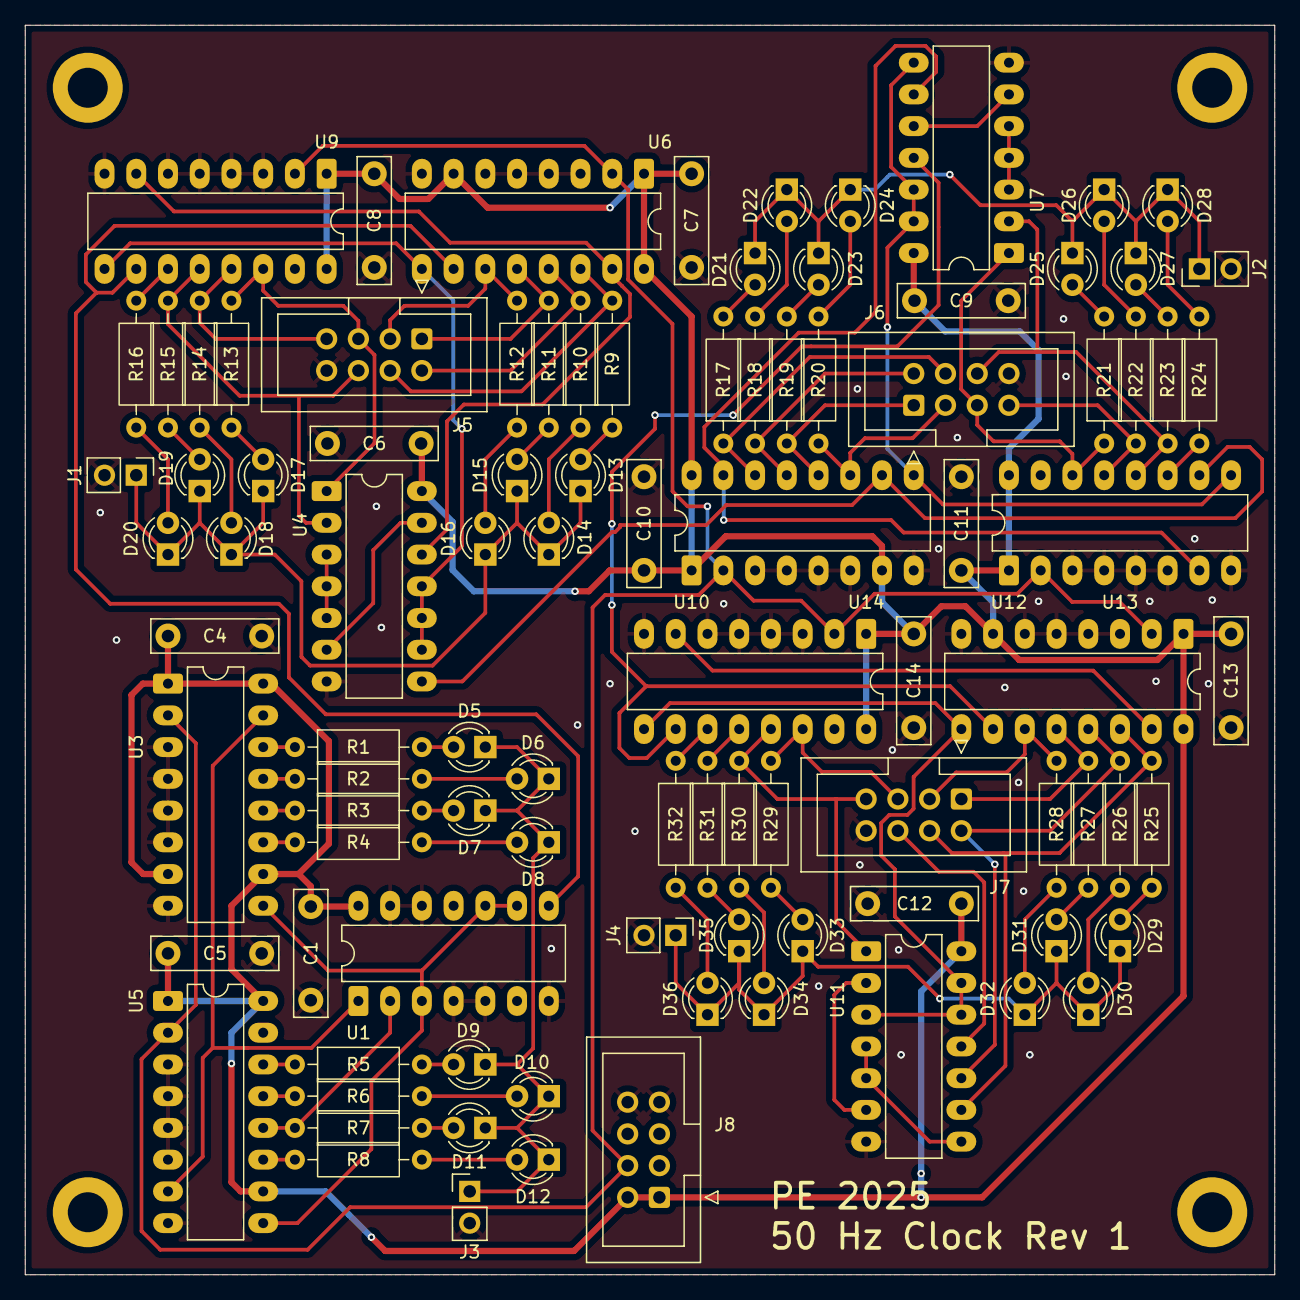
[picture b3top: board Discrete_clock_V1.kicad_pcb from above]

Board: 2 copper layers, 100.0 x 100.0 mm, 100 parts (0 on the bottom side), 89 nets.

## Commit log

2025-11-06 added sim file
2025-11-06 added components list
2026-01-20 add pcb V1
